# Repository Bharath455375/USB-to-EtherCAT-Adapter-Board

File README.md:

## USB-to-EtherCAT-Adapter-Board

A USB-to-EtherCAT Adapter Board V1.0, intended to provide communication between a USB host system and an EtherCAT 
network. The board combines an STM32F411CEUx microcontroller for USB interfacing 
and control with the LAN9252 EtherCAT controller for handling EtherCAT
communication. It provides a compact hardware interface for converting USB communication into EtherCAT communication, making it suitable for industrial automation applications.

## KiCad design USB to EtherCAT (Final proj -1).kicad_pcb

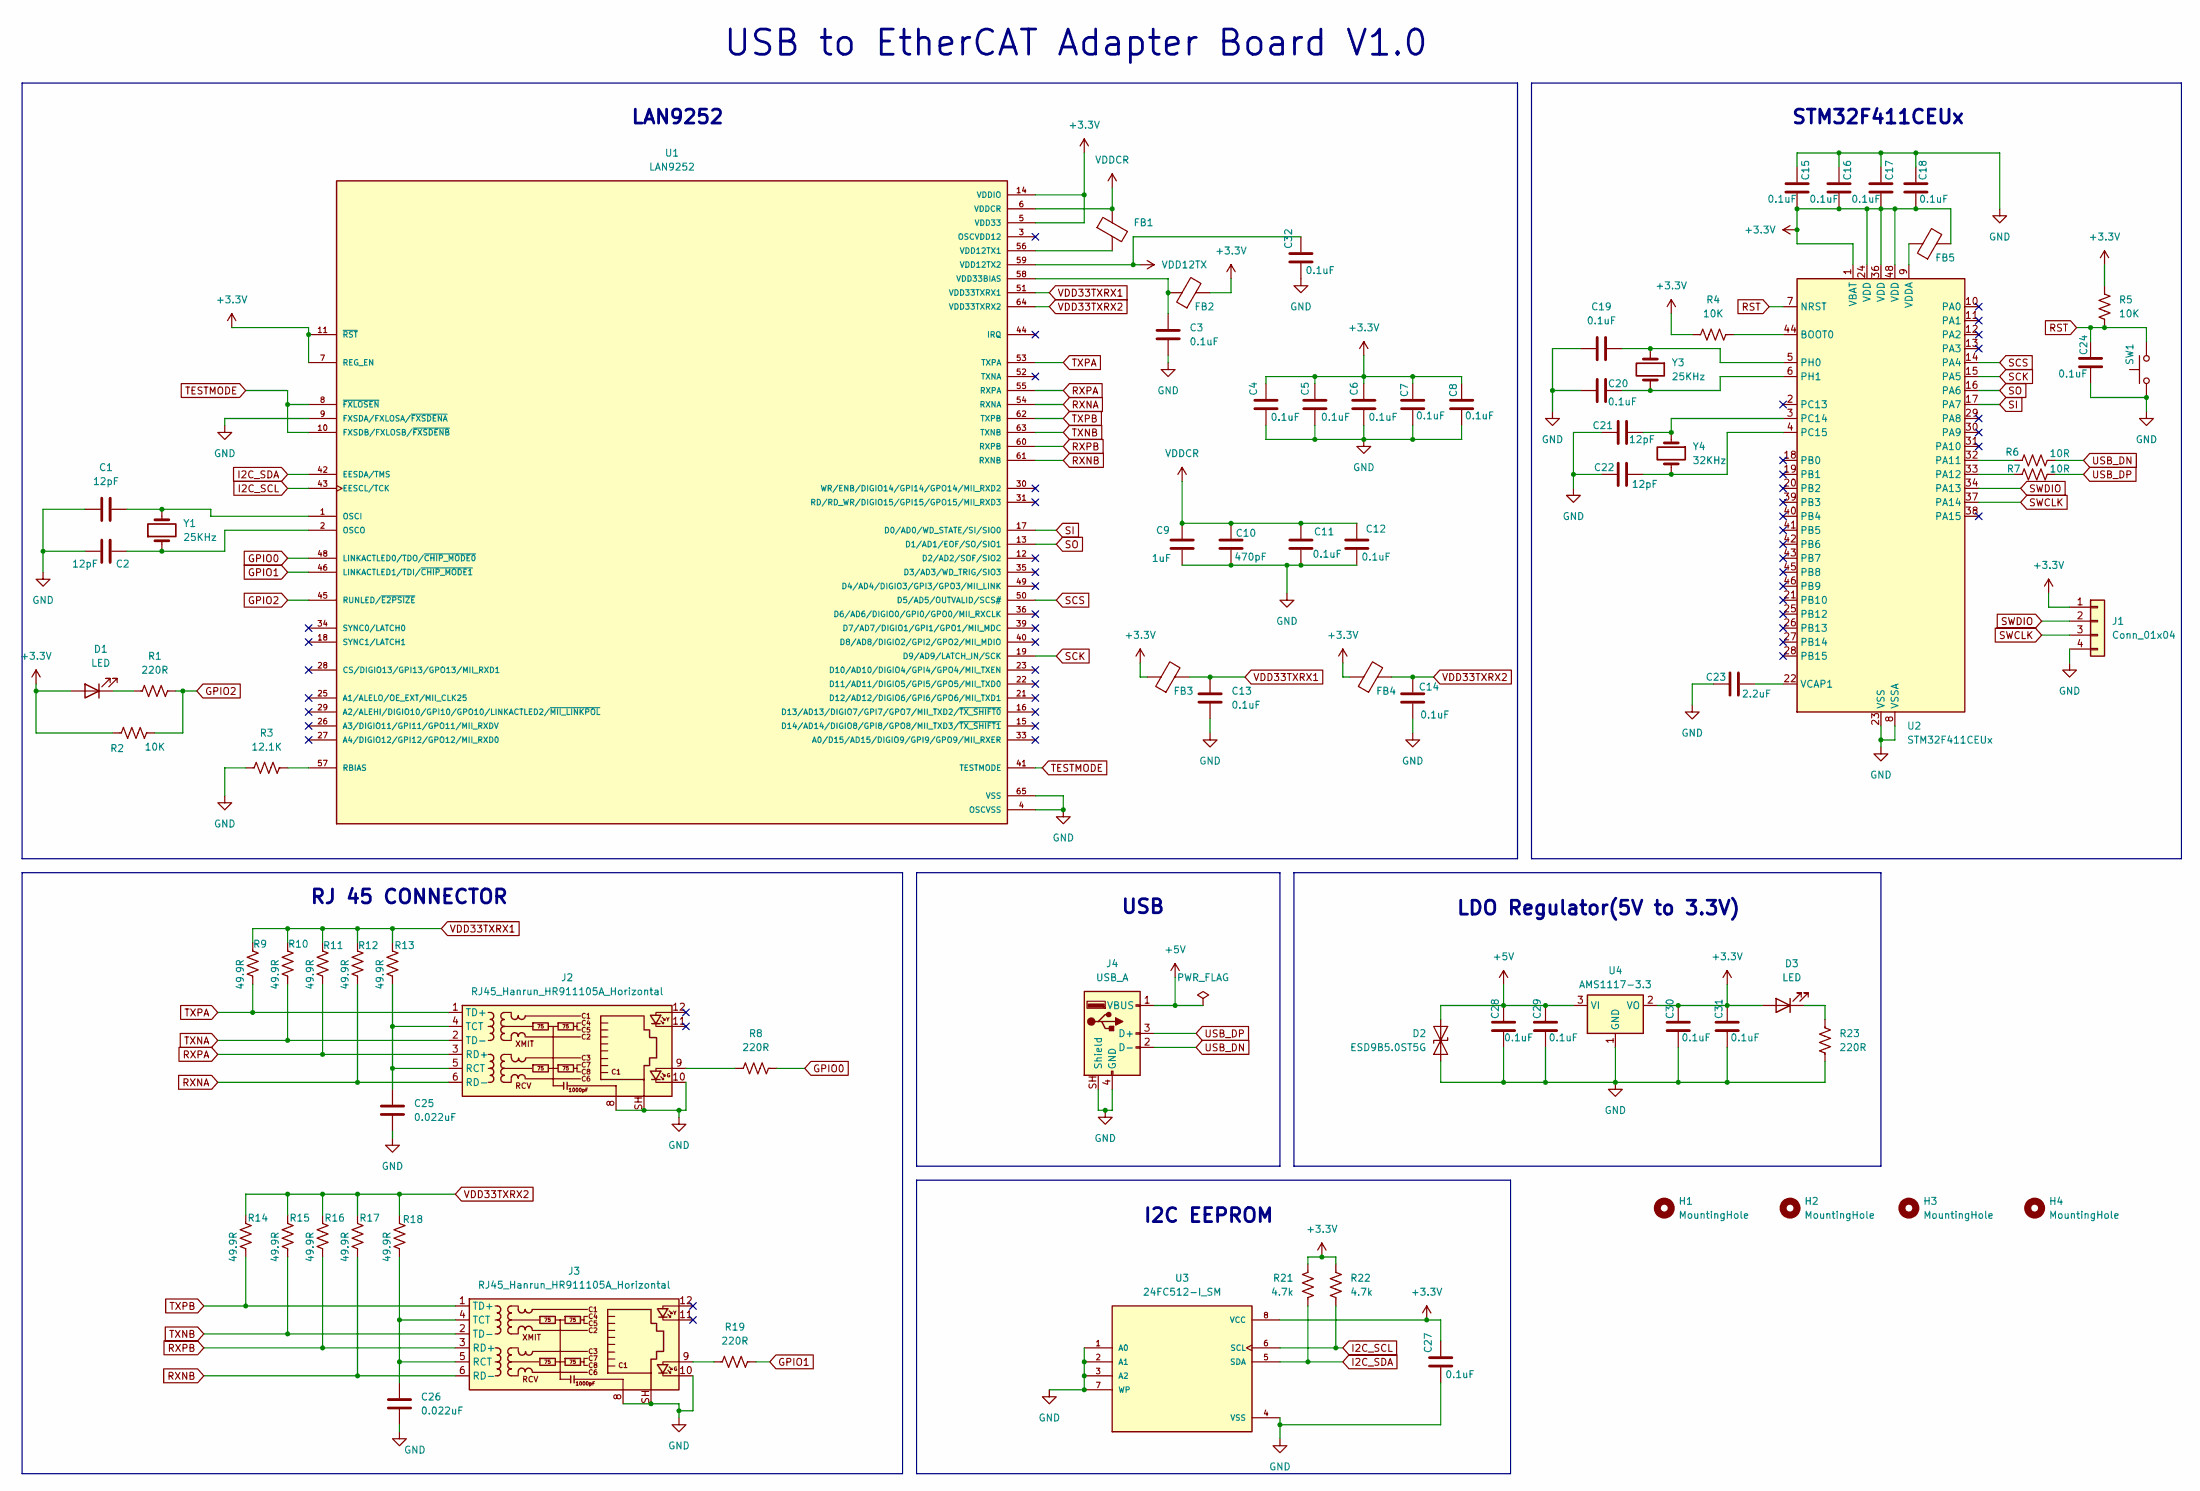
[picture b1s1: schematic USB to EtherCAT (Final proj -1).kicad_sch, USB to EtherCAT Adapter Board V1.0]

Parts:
C1, C2, C21, C22: 12pF; C_0805_2012Metric_Pad1.18x1.45mm_HandSolder
C3, C4, C5, C6, C7, C8, C11, C12, C13, C14, C15, C16, C17, C18, C19, C20, C24, C27, C28, C29, C30, C31, C32: 0.1uF; C_0805_2012Metric_Pad1.18x1.45mm_HandSolder
C9: 1uF; C_0805_2012Metric_Pad1.18x1.45mm_HandSolder
C10: 470pF; C_0805_2012Metric_Pad1.18x1.45mm_HandSolder
C23: 2.2uF; C_0805_2012Metric_Pad1.18x1.45mm_HandSolder
C25, C26: 0.022uF; C_0805_2012Metric_Pad1.18x1.45mm_HandSolder
D1, D3: LED; LED_0805_2012Metric_Pad1.15x1.40mm_HandSolder
D2: ESD9B5.0ST5G; D_SOD-923
FB1, FB2, FB3, FB4, FB5: FerriteBead; L_0805_2012Metric_Pad1.05x1.20mm_HandSolder
H1, H2, H3, H4: MountingHole; MountingHole_2.2mm_M2
J1: Conn_01x04; PinHeader_1x04_P2.54mm_Vertical
J2, J3: RJ45_Hanrun_HR911105A_Horizontal
J4: USB_A; USB_A_Molex_67643_Horizontal
R1, R8, R19, R23: 220R; R_0805_2012Metric_Pad1.20x1.40mm_HandSolder
R2, R4, R5: 10K; R_0805_2012Metric_Pad1.20x1.40mm_HandSolder
R3: 12.1K; R_0805_2012Metric_Pad1.20x1.40mm_HandSolder
R6, R7: 10R; R_0805_2012Metric_Pad1.20x1.40mm_HandSolder
R9, R10, R11, R12, R13, R14, R15, R16, R17, R18: 49.9R; R_0805_2012Metric_Pad1.20x1.40mm_HandSolder
R21, R22: 4.7k; R_0805_2012Metric_Pad1.20x1.40mm_HandSolder
SW1: SW_Push; SW_Push_1P1T_NO_E-Switch_TL3301NxxxxxG
U1: LAN9252; QFP50P1200X1200X120-65N; PARTREV 04-08-15
U2: STM32F411CEUx; QFN-48-1EP_7x7mm_P0.5mm_EP5.6x5.6mm
U3: 24FC512-I_SM; SOIC127P794X203-8N; PARTREV Q
U4: AMS1117-3.3; SOT-223-3_TabPin2
Y1, Y3: 25KHz; Crystal_HC49-4H_Vertical
Y4: 32KHz; Crystal_SMD_3225-4Pin_3.2x2.5mm

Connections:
+3.3V: C4.1, C5.1, C6.1, C7.1, C8.1, C15.2, C16.2, C17.2, C18.2, C27.1, C30.1, C31.1, D1.2 (A), D3.2 (A), FB2.2, FB3.1, FB4.1, FB5.2, J1.1, R2.1, R4.1, R5.1, R21.2, R22.1, U1.5 (VDD33), U1.7 (REG_EN), U1.11 (~RST), U1.14 (VDDIO), U1.20 (VDDIO), U1.32 (VDDIO), U1.37 (VDDIO), U1.47 (VDDIO), U2.1 (VBAT), U2.24 (VDD), U2.36 (VDD), U2.48 (VDD), U3.8 (VCC), U4.2 (VO)
+5V: C28.1, C29.1, D2.2 (A2), J4.1 (VBUS), U4.3 (VI)
GND: C1.1, C2.2, C3.2, C4.2, C5.2, C6.2, C7.2, C8.2, C9.2, C10.2, C11.2, C12.2, C13.2, C14.2, C15.1, C16.1, C17.1, C18.1, C19.2, C20.2, C21.2, C22.2, C23.2, C24.2, C25.2, C26.2, C27.2, C28.2, C29.2, C30.2, C31.2, C32.2, D2.1 (A1), J1.4, J2.8, J2.10, J2.SH, J3.8, J3.10, J3.SH, J4.4 (GND), J4.SH (Shield), R3.1, R23.2, SW1.2, U1.4 (OSCVSS), U1.9 (FXSDA/FXLOSA/~FXSDENA), U1.65 (VSS), U2.8 (VSSA), U2.23 (VSS), U2.35 (VSS), U2.47 (VSS), U2.49 (VSS), U3.1 (A0), U3.2 (A1), U3.3 (A2), U3.4 (VSS), U3.7 (WP), U4.1 (GND)
GPIO0: R8.2, U1.48 (LINKACTLED0/TDO/~CHIP_MODE0)
GPIO1: R19.2, U1.46 (LINKACTLED1/TDI/~CHIP_MODE1)
GPIO2: R1.2, R2.2, U1.45 (RUNLED/~E2PSIZE)
I2C_SCL: R22.2, U1.43 (EESCL/TCK), U3.6 (SCL)
I2C_SDA: R21.1, U1.42 (EESDA/TMS), U3.5 (SDA)
unnamed: D1.1 (K), R1.1
unnamed: D3.1 (K), R23.1
unnamed: J2.9, R8.1
unnamed: C25.1, J2.4 (TCT), J2.5 (RCT), R13.1
unnamed: J3.9, R19.1
unnamed: C26.1, J3.4 (TCT), J3.5 (RCT), R18.1
unnamed: C1.2, U1.1 (OSCI), Y1.2
unnamed: C2.1, U1.2 (OSCO), Y1.1
unnamed: R3.2, U1.57 (RBIAS)
unnamed: FB1.2, U1.56 (VDD12TX1)
unnamed: C3.1, FB2.1, U1.58 (VDD33BIAS)
unnamed: R4.2, U2.44 (BOOT0)
unnamed: R6.1, U2.32 (PA11)
unnamed: R7.1, U2.33 (PA12)
unnamed: C21.1, U2.3 (PC14), Y4.1
unnamed: C22.1, U2.4 (PC15), Y4.2
unnamed: C19.1, U2.5 (PH0), Y3.1
unnamed: C20.1, U2.6 (PH1), Y3.2
unnamed: C23.1, U2.22 (VCAP1)
unnamed: FB5.1, U2.9 (VDDA)
RST: C24.1, R5.2, SW1.1, U2.7 (NRST)
RXNA: J2.6 (RD-), R12.1, U1.54 (RXNA)
RXNB: J3.6 (RD-), R17.1, U1.61 (RXNB)
RXPA: J2.3 (RD+), R11.1, U1.55 (RXPA)
RXPB: J3.3 (RD+), R16.1, U1.60 (RXPB)
SCK: U1.19 (D9/AD9/LATCH_IN/SCK), U2.15 (PA5)
SCS: U1.50 (D5/AD5/OUTVALID/SCS#), U2.14 (PA4)
SI: U1.17 (D0/AD0/WD_STATE/SI/SIO0), U2.17 (PA7)
SO: U1.13 (D1/AD1/EOF/SO/SIO1), U2.16 (PA6)
SWCLK: J1.3, U2.37 (PA14)
SWDIO: J1.2, U2.34 (PA13)
TESTMODE: U1.8 (~FXLOSEN), U1.10 (FXSDB/FXLOSB/~FXSDENB), U1.41 (TESTMODE)
TXNA: J2.2 (TD-), R10.1
TXNB: J3.2 (TD-), R15.1, U1.63 (TXNB)
TXPA: J2.1 (TD+), R9.1, U1.53 (TXPA)
TXPB: J3.1 (TD+), R14.1, U1.62 (TXPB)
USB_DN: J4.2 (D-), R6.2
USB_DP: J4.3 (D+), R7.2
VDD12TX: C32.1, U1.59 (VDD12TX2)
VDD33TXRX1: C13.1, FB3.2, R9.2, R10.2, R11.2, R12.2, R13.2, U1.51 (VDD33TXRX1)
VDD33TXRX2: C14.1, FB4.2, R14.2, R15.2, R16.2, R17.2, R18.2, U1.64 (VDD33TXRX2)
VDDCR: C9.1, C10.1, C11.1, C12.1, FB1.1, U1.6 (VDDCR), U1.24 (VDDCR), U1.38 (VDDCR)

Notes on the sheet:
I2C EEPROM
USB to EtherCAT Adapter Board V1.0
RJ 45 CONNECTOR
LDO Regulator(5V to 3.3V)
LAN9252
USB
STM32F411CEUx

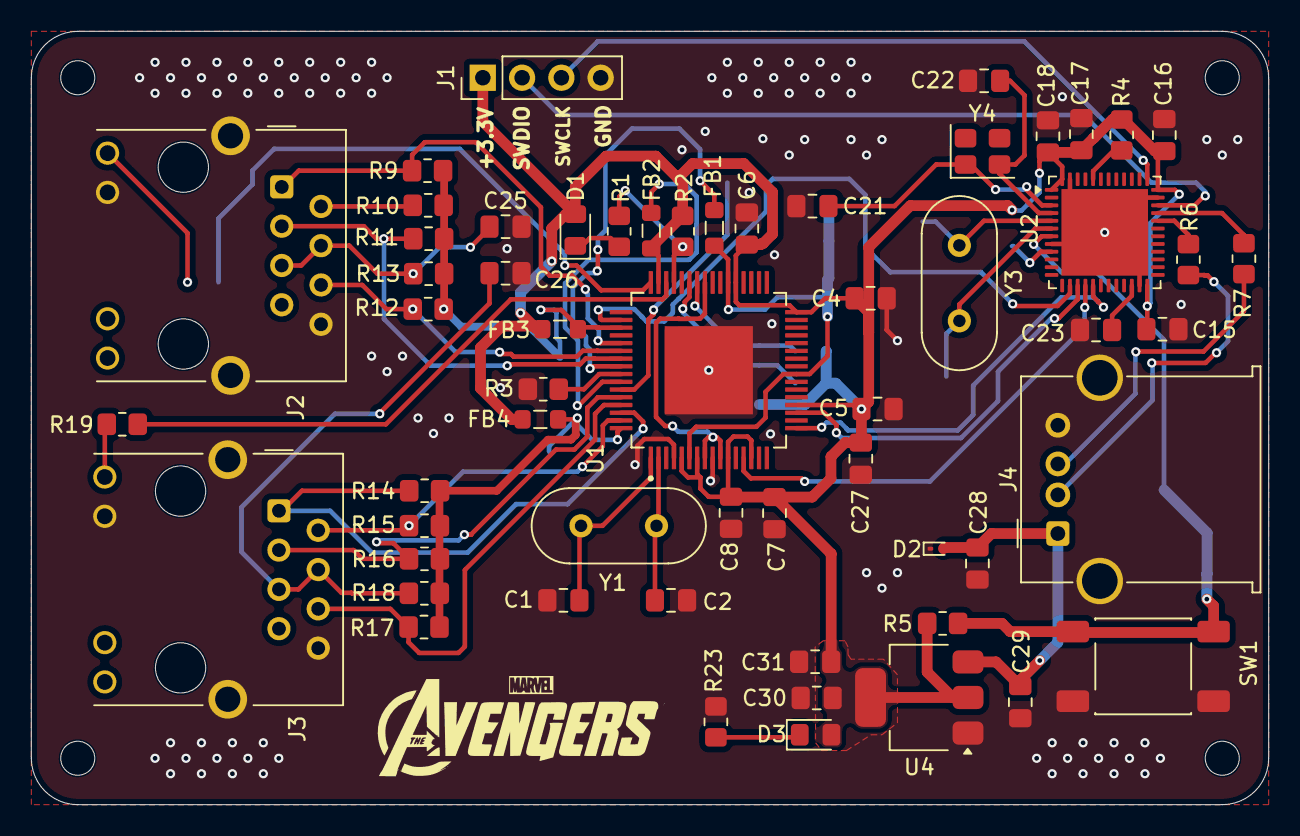
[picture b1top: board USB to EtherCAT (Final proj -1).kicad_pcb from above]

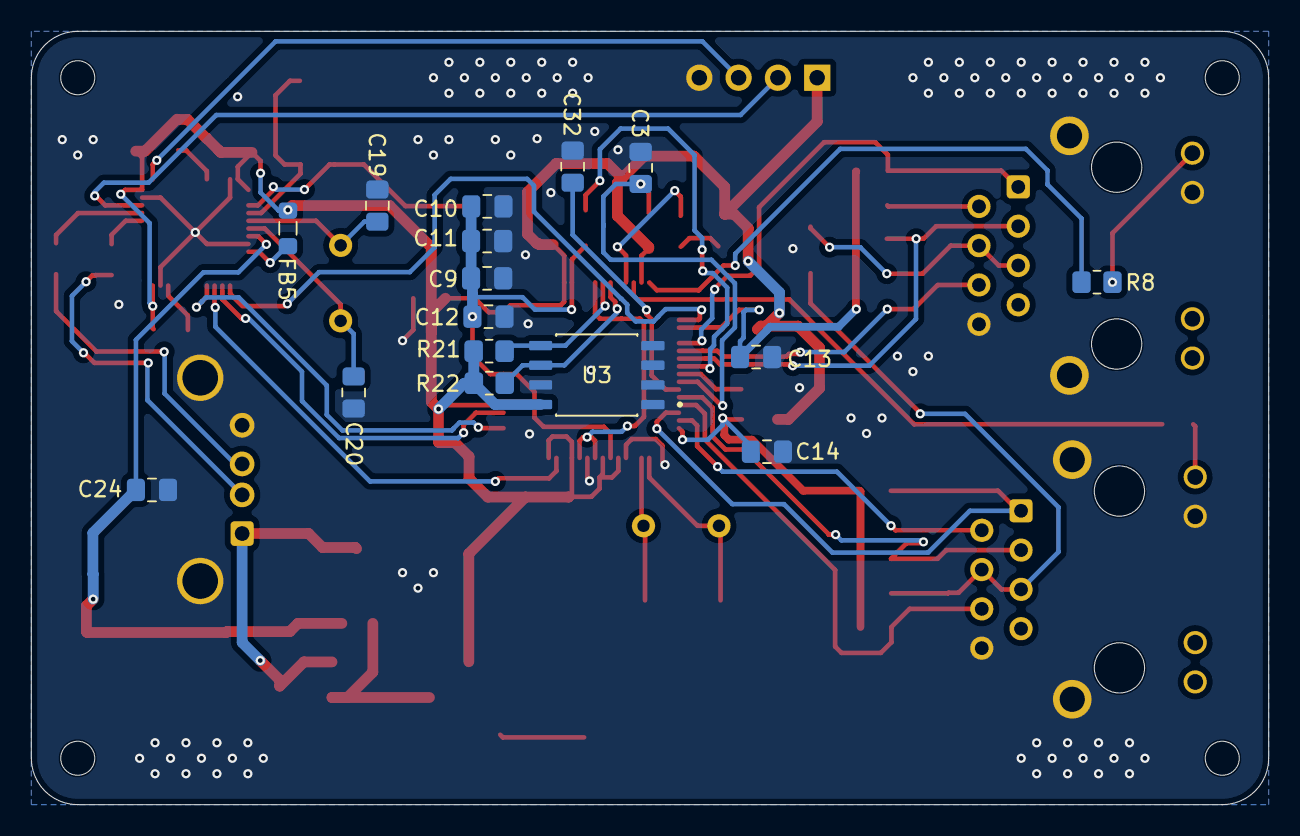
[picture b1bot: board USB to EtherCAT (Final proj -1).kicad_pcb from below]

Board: 2 copper layers, 80.0 x 50.0 mm, 78 parts (16 on the bottom side), 50 nets.

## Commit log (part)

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2026-04-10 Added folder
